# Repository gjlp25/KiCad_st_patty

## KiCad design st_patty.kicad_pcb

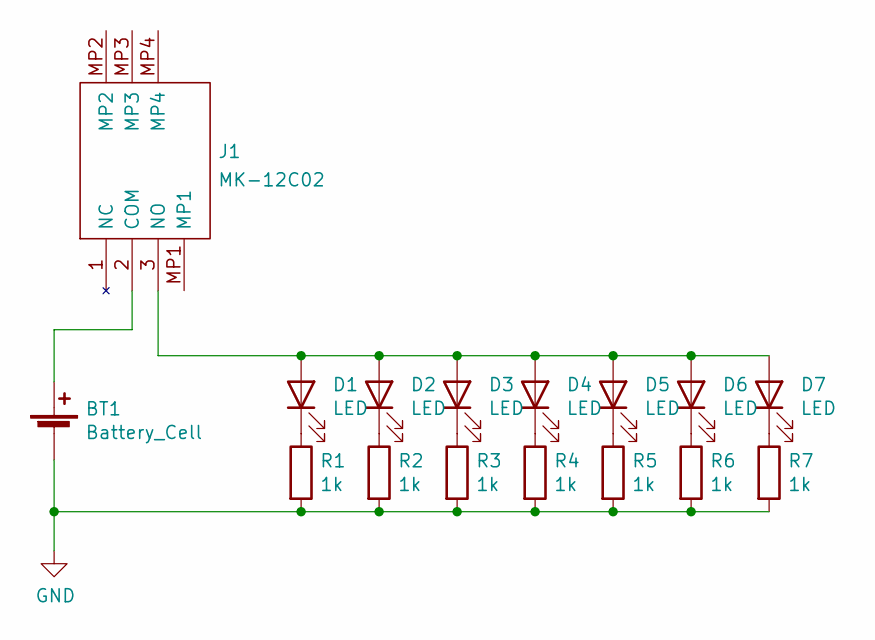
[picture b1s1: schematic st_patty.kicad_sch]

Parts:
BT1: Battery_Cell; CR2032_holder_ali
D1, D2, D3, D4, D5, D6, D7: LED; LED_0805_2012Metric_Pad1.15x1.40mm_HandSolder
J1: MK-12C02; MK12C02; Manufacturer_Part_Number MK-12C02
R1, R2, R3, R4, R5, R6, R7: 1k; R_0805_2012Metric_Pad1.20x1.40mm_HandSolder

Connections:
GND: BT1.2 (-), R1.2, R2.2, R3.2, R4.2, R5.2, R6.2, R7.2
unnamed: BT1.1 (+), J1.2 (COM)
unnamed: D1.1 (K), R1.1
unnamed: D1.2 (A), D2.2 (A), D3.2 (A), D4.2 (A), D5.2 (A), D6.2 (A), D7.2 (A), J1.3 (NO)
unnamed: D2.1 (K), R2.1
unnamed: D3.1 (K), R3.1
unnamed: D4.1 (K), R4.1
unnamed: D5.1 (K), R5.1
unnamed: D6.1 (K), R6.1
unnamed: D7.1 (K), R7.1

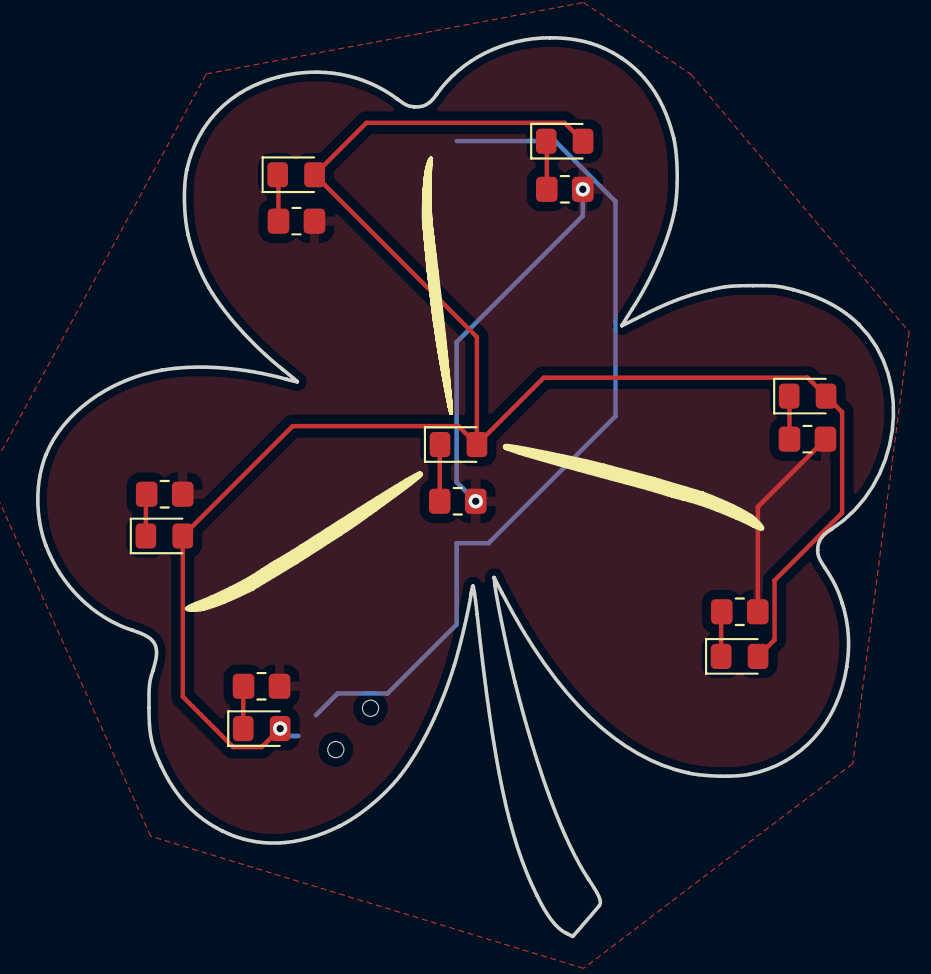
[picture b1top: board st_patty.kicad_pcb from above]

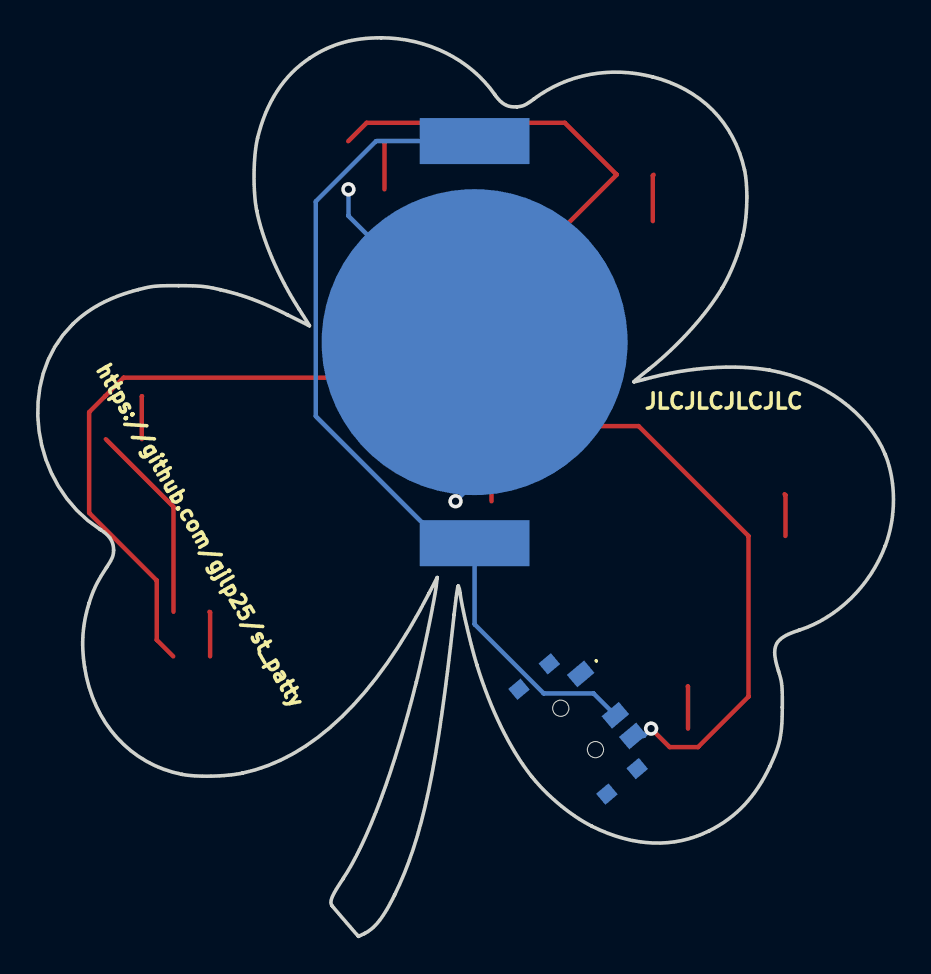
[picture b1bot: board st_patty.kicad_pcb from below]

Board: 2 copper layers, 47.5 x 49.9 mm, 16 parts (2 on the bottom side), 10 nets.
